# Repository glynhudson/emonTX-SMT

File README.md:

emonTX-SMT
==========

Very early prototype 

openenergymonitor.org

http://openenergymonitor.blogspot.co.uk/search/label/emonTxSMT
http://openenergymonitor.org/emon/node/736

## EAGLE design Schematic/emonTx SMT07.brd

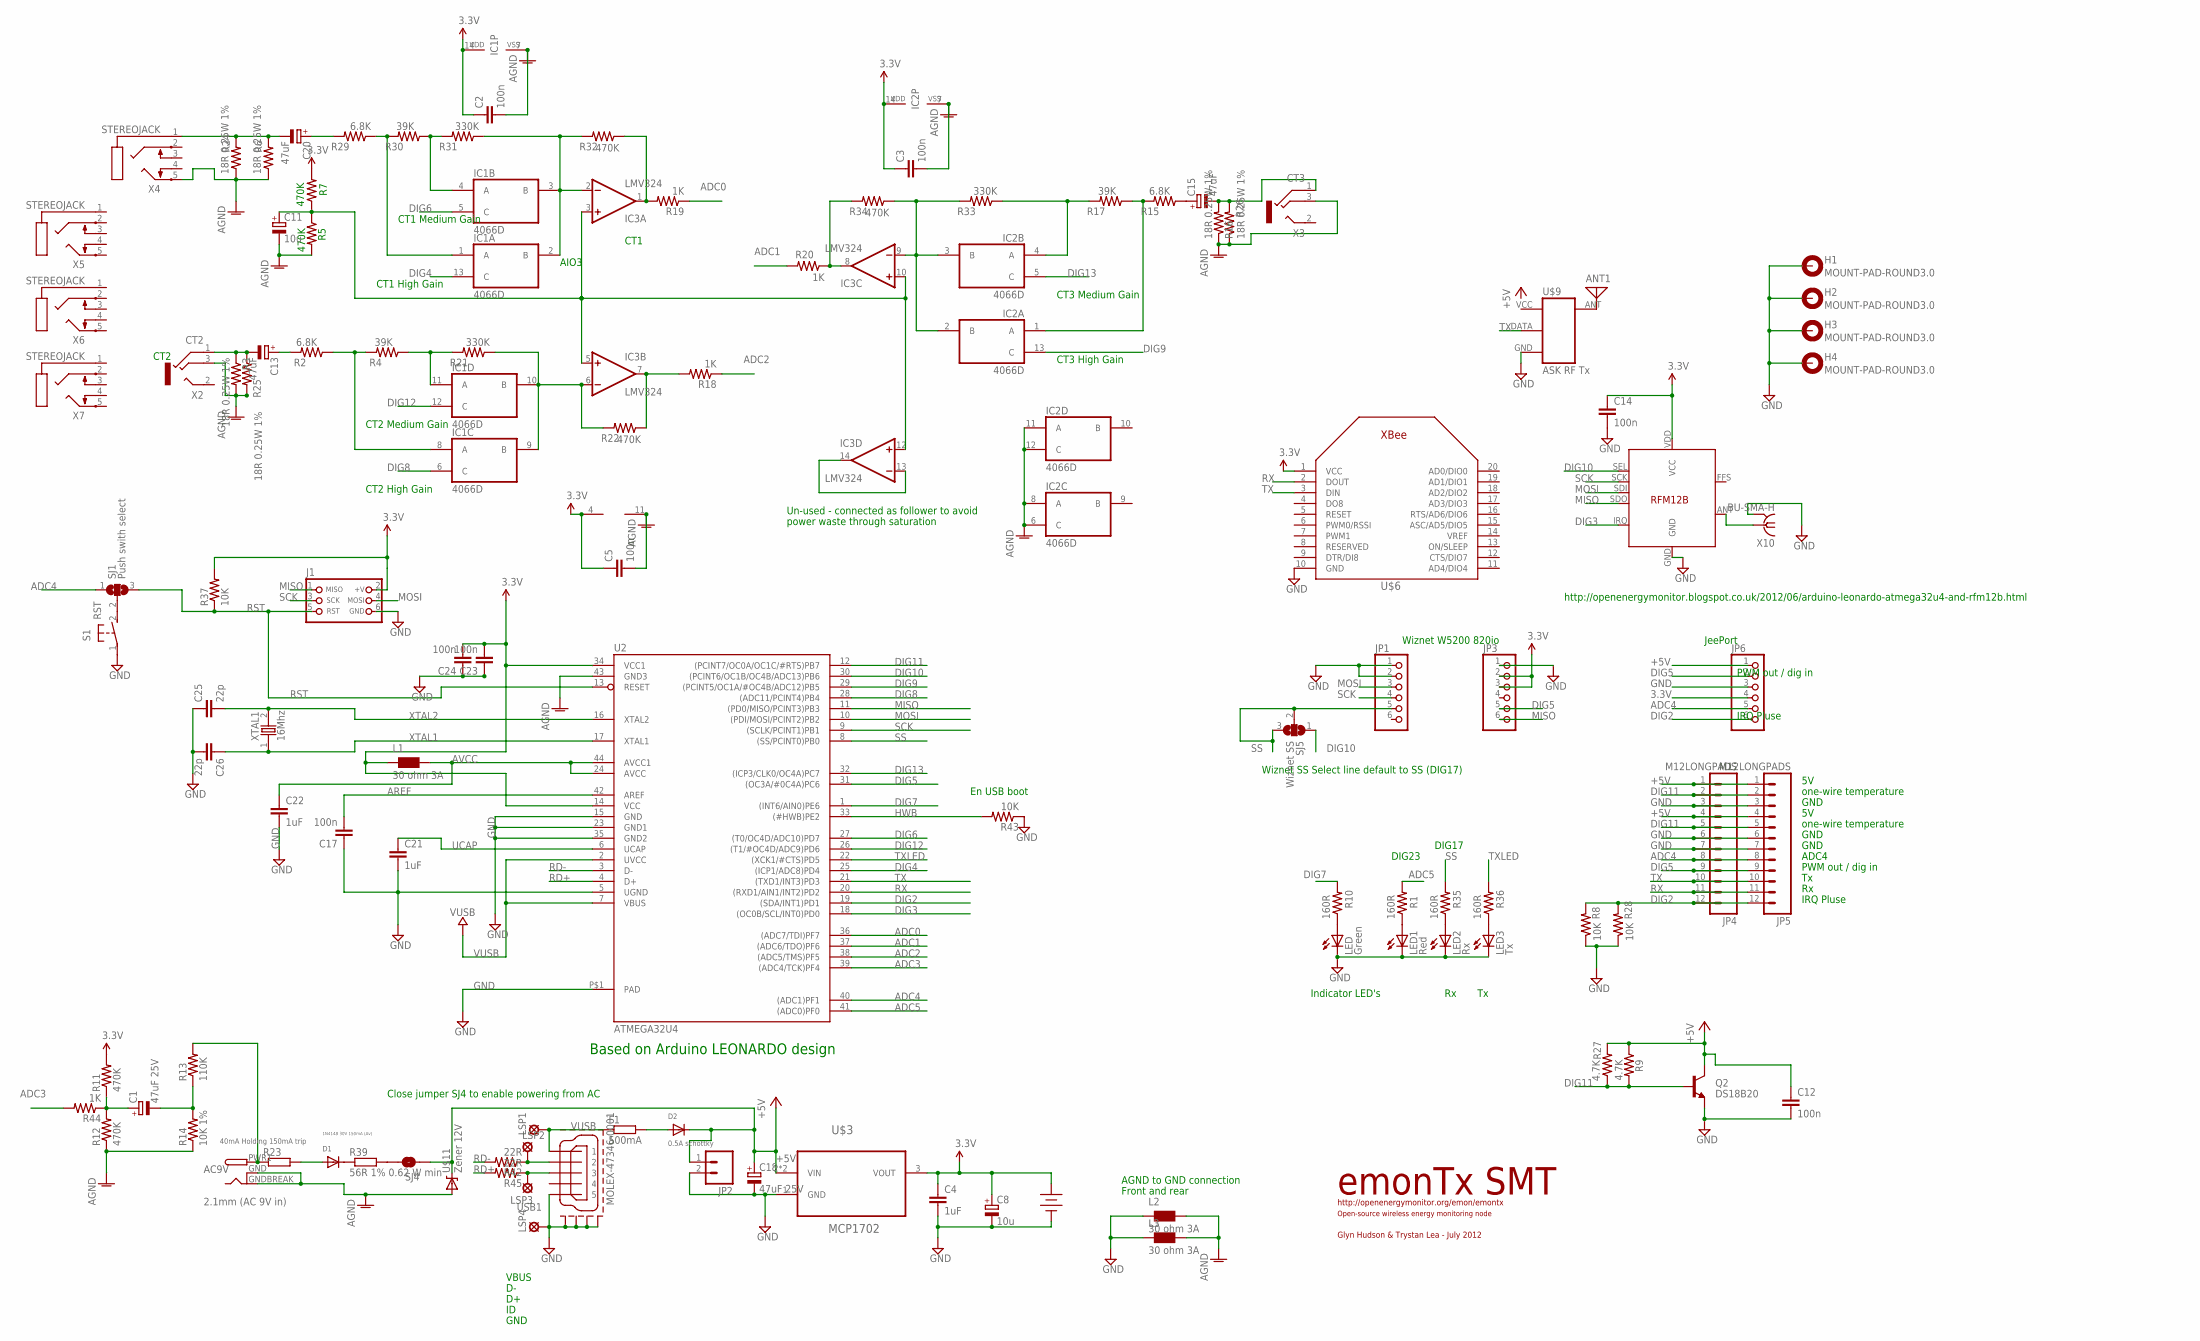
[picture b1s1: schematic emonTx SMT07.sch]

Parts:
3XAAA: 4.5V; AAA_PCB_HOLDER
AC9V: 2.1mm (AC 9V in); DCJACK_2MM_SMT
ANT1: ANTENNA; PAD-01
C1, C18: 47uF 25V; PANASONIC_D
C2, C3, C5, C12, C14, C17, C23, C24: 100n; 0603-CAP
C4: 1uF; C0603
C8, C11: 10u; PANASONIC_B
C13, C15, C20: 47uF; PANASONIC_D
C21: 1uF; 0603-CAP
C22: 1uF; C0603-ROUND
C25, C26: 22p; 0603-CAP
D1: 1N4148 30V 150mA (Av); SOD-323F
D2: 0.5A schottky; SOD-123
F1: 500mA; R1210
H1, H2, H3, H4: MOUNT-PAD-ROUND3.0; 3,0-PAD
IC1, IC2: 4066D; SO14
IC3: LMV324; SO14
J1: CON_HEADER_PRG_AVR_ICSP; HEADER_PRG_2X03
JP1, JP3, JP6: PINHD-1X6; 1X06
JP2: M02LOCK_LONGPADS; 1X02_LOCK_LONGPADS
JP4, JP5: M12LONGPADS; 1X12_LONGPADS
L1, L2, L3: 30 ohm 3A; 0603
LED: Green; CHIPLED_0603
LED1: Red; CHIPLED_0603
LED2: Rx; CHIPLED_0603
LED3: Tx; CHIPLED_0603
LSP1, LSP2, LSP3, LSP4: LSP11
Q2: DS18B20; TO-92
R1, R10, R35, R36: 160R; 0603-RES
R2, R15, R29: 6.8K; 0603-RES
R3, R6, R16: 18R 0.25W 1%; 1206
R4, R17, R30: 39K; 0603-RES
R5, R7, R11, R12, R22, R32, R34: 470K; 0603-RES
R8, R37, R43: 10K; 0603-RES
R9: 4.7K; 1206
R13: 110K; 0603-RES
R14: 10K 1%; 0603-RES
R18, R19, R20, R44: 1K; 0603-RES
R21, R31, R33: 330K; 0603-RES
R23: 40mA Holding 150mA trip; R1210
R24, R25, R26: 18R 0.25W 1%; AXIAL-0.4
R27: 4.7K; AXIAL-0.4
R28: 10K; AXIAL-0.4
R39: 56R 1% 0.62 W min; RESISTOR_R2010
R42, R45: 22R; 0603-RES
S1: RST; B3F-31XX
SJ1: Push swith select; SJ_2W
SJ4: SOLDERJUMPER-OLDNO; SJ_2S-NO
SJ5: Wiznet SS; SJ_2W
U2: ATMEGA32U4; TQFP44-PAD
U$1: RFM12B
U$3: MCP1702; SOT89
U$6: XBEE
U$9: ASK RF Tx; RF-LINK_TX
U$11: Zener 12V; SOD-323
USB1: MOLEX-47346-0001; MOLEX-47364-0001
X2: CT2; 1503_02
X3: CT3; 1503_02
X4, X5, X6, X7: STEREOJACK; STX3100
X10: BU-SMA-H
XTAL1: 16Mhz; HC-49U

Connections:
3.3V: 3XAAA.+, C2.1, C3.1, C4.1, C5.1, C8.+, C14.1, C23.2, C24.2, IC1.14 (VDD), IC2.14 (VDD), IC3.4 (V+), J1.2 (+V), JP3.2, JP3.3, JP6.4, L1.1, R7.2, R11.2, R37.2, U2.14 (VCC), U2.34 (VCC1), U$1.VDD (VCC), U$3.3 (VOUT), U$6.1 (VCC)
+5V: C12.1, C18.+, D2.C, JP2.1, JP4.1, JP4.4, JP5.1, JP5.4, JP6.1, Q2.3 (C), R9.1, R27.P$2 (2), SJ4.1, U$3.2 (VIN), U$3.2.1 (VIN), U$9.VCC (+5V), U$11.1 (C)
ADC0: R19.1, U2.36 ((ADC7/TDI)PF7)
ADC1: R20.2, U2.37 ((ADC6/TDO)PF6)
ADC2: R18.1, U2.38 ((ADC5/TMS)PF5)
ADC3: R44.2, U2.39 ((ADC4/TCK)PF4)
ADC4: JP4.8, JP5.8, JP6.5, SJ1.1, U2.40 ((ADC1)PF1)
ADC5: R1.2, U2.41 ((ADC0)PF0)
AGND: AC9V.GND (GNDBREAK), AC9V.GNDBREAK (GND), C2.2, C3.2, C5.2, C11.-, IC1.7 (VSS), IC2.6 (C), IC2.7 (VSS), IC2.8 (A), IC2.11 (A), IC2.12 (C), IC3.11 (V-), L2.2, L3.2, R3.2, R5.2, R6.1, R12.1, R14.1, R16.1, R24.P$1 (1), R25.P$2 (2), R26.P$1 (1), U2.43 (GND3), U$11.2 (A), X2.3, X3.3, X4.5
AREF: C17.2, U2.42 (AREF)
AVCC: C22.1, L1.2, U2.24 (AVCC), U2.44 (AVCC1)
DIG2: JP4.12, JP5.12, JP6.6, R8.2, R28.P$2 (2), U2.19 ((SDA/INT1)PD1)
DIG3: U2.18 ((OC0B/SCL/INT0)PD0), U$1.IRQ
DIG4: IC1.13 (C), U2.25 ((ICP1/ADC8)PD4)
DIG5: JP3.5, JP4.9, JP5.9, JP6.2, U2.31 ((OC3A/#0C4A)PC6)
DIG6: IC1.5 (C), U2.27 ((T0/OC4D/ADC10)PD7)
DIG7: R10.2, U2.1 ((INT6/AIN0)PE6)
DIG8: IC1.6 (C), U2.28 ((ADC11/PCINT4)PB4)
DIG9: IC2.13 (C), U2.29 ((PCINT5/OC1A/#OC4B/ADC12)PB5)
DIG10: SJ5.1, U2.30 ((PCINT6/OC1B/OC4B/ADC13)PB6), U$1.SEL
DIG11: JP4.2, JP4.5, JP5.2, JP5.5, Q2.2 (B), R9.2, R27.P$1 (1), U2.12 ((PCINT7/OC0A/OC1C/#RTS)PB7)
DIG12: IC1.12 (C), U2.26 ((T1/#OC4D/ADC9)PD6)
DIG13: IC2.5 (C), U2.32 ((ICP3/CLK0/OC4A)PC7)
GND: 3XAAA.-, C4.2, C8.-, C12.2, C14.2, C17.1, C18.-, C21.2, C22.2, C23.1, C24.1, C25.1, C26.2, H1.B3,0, H2.B3,0, H3.B3,0, H4.B3,0, J1.6 (GND), JP1.1, JP1.2, JP2.2, JP3.1, JP4.3, JP4.6, JP4.7, JP5.3, JP5.6, JP5.7, JP6.3, L2.1, L3.1, LED.C, LED1.C, LED2.C, LED3.C, LSP4.MP, Q2.1 (E), R8.1, R28.P$1 (1), R43.1, S1.1, U2.5 (UGND), U2.15 (GND), U2.23 (GND1), U2.35 (GND2), U2.P$1 (PAD), U$1.GND, U$3.1 (GND), U$6.10 (GND), U$9.GND, USB1.5, USB1.GND1, USB1.GND2, USB1.GND3, USB1.GND4, X10.2 (GND), X10.3 (GND), X10.4 (GND), X10.5 (GND)
HWB: R43.2, U2.33 ((#HWB)PE2)
MISO: J1.1 (MISO), JP3.6, U2.11 ((PD0/MISO/PCINT3)PB3), U$1.SDO
MOSI: J1.4 (MOSI), JP1.3, U2.10 ((PDI/MOSI/PCINT2)PB2), U$1.SDI
unnamed: S1.2 (S), SJ1.2
unnamed: LED.A, R10.1
unnamed: AC9V.PWR1 (PWR), R13.2, R23.1
unnamed: D2.A, F1.2
unnamed: C1.-, R13.1, R14.2
unnamed: D1.C, R39.1
unnamed: C20.+, R29.2
unnamed: LED1.A, R1.1
unnamed: C1.+, R11.1, R12.2, R44.1
unnamed: R39.2, SJ4.2
unnamed: ANT1.1, U$9.ANT
unnamed: LSP2.MP, R42.1, USB1.2
unnamed: U$1.ANT, X10.1
unnamed: C15.-, R16.2, R26.P$2 (2), X3.1
unnamed: LSP3.MP, R45.1, USB1.3
unnamed: IC1.4 (A), R30.1, R31.2
unnamed: IC1.1 (A), R29.1, R30.2
unnamed: C13.+, R2.2
unnamed: LED2.A, R35.1
unnamed: C13.-, R3.1, R25.P$1 (1), X2.1
unnamed: C20.-, R6.2, R24.P$2 (2), X4.1
unnamed: C11.+, IC3.3 (+IN), IC3.5 (+IN), IC3.10 (+IN), IC3.12 (+IN), R5.1, R7.1
unnamed: C15.+, R15.1
unnamed: IC1.8 (A), R2.1, R4.2
unnamed: IC1.11 (A), R4.1, R21.2
unnamed: IC3.7 (OUT), R18.2, R22.1
unnamed: IC1.9 (B), IC1.10 (B), IC3.6 (-IN), R21.1, R22.2
unnamed: IC1.2 (B), IC1.3 (B), IC3.2 (-IN), R31.1, R32.2
unnamed: IC3.1 (OUT), R19.2, R32.1
unnamed: LED3.A, R36.1
unnamed: IC2.2 (B), IC2.3 (B), IC3.9 (-IN), R33.2, R34.1
unnamed: IC3.13 (-IN), IC3.14 (OUT)
unnamed: IC3.8 (OUT), R20.1, R34.2
unnamed: IC2.1 (A), R15.2, R17.1
unnamed: IC2.4 (A), R17.2, R33.1
unnamed: D1.A, R23.2
RD+: R45.2, U2.4 (D+)
RD-: R42.2, U2.3 (D-)
RST: J1.5 (RST), R37.1, SJ1.3, U2.13 (RESET)
RX: JP4.11, JP5.11, U2.20 ((RXD1/AIN1/INT2)PD2), U$6.2 (DOUT)
SCK: J1.3 (SCK), JP1.4, U2.9 ((SCLK/PCINT1)PB1), U$1.SCK
SS: JP1.5, R35.2, SJ5.2, SJ5.3, U2.8 ((SS/PCINT0)PB0)
TX: JP4.10, JP5.10, U2.21 ((TXD1/INT3)PD3), U$6.3 (DIN), U$9.DATA
TXLED: R36.2, U2.22 ((XCK1/#CTS)PD5)
UCAP: C21.1, U2.6 (UCAP)
VUSB: F1.1, LSP1.MP, U2.2 (UVCC), U2.7 (VBUS), USB1.1
XTAL1: C26.1, U2.17 (XTAL1), XTAL1.1
XTAL2: C25.2, U2.16 (XTAL2), XTAL1.2

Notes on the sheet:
CT2
CT1
http://openenergymonitor.org/emon/emontx
Open-source wireless energy monitoring node
emonTx SMT
Glyn Hudson & Trystan Lea - July 2012
AIO3
Based on Arduino LEONARDO design
Wiznet W5200 820io
Close jumper SJ4 to enable powering from AC
En USB boot
Wiznet SS Select line default to SS (DIG17)
CT1 High Gain
CT1 Medium Gain
DIG23
http://openenergymonitor.blogspot.co.uk/2012/06/arduino-leonardo-atmega32u4-and-rfm12b.html
CT2 Medium Gain
CT2 High Gain
CT3 Medium Gain
CT3 High Gain
PWM out / dig in
IRQ Pluse
AGND to GND connection
Front and rear
ADC4
one-wire temperature
GND
VBUS
Indicator LED's
Rx Tx
Un-used - connected as follower to avoid
power waste through saturation
DIG17
JeePort

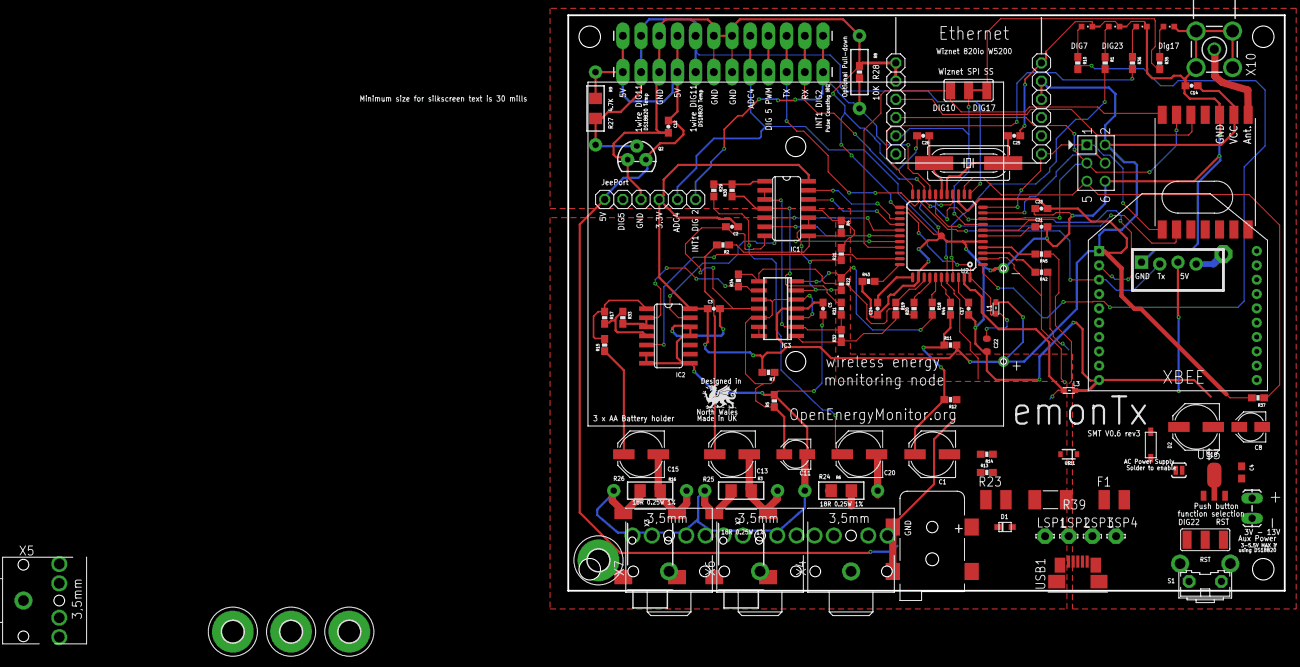
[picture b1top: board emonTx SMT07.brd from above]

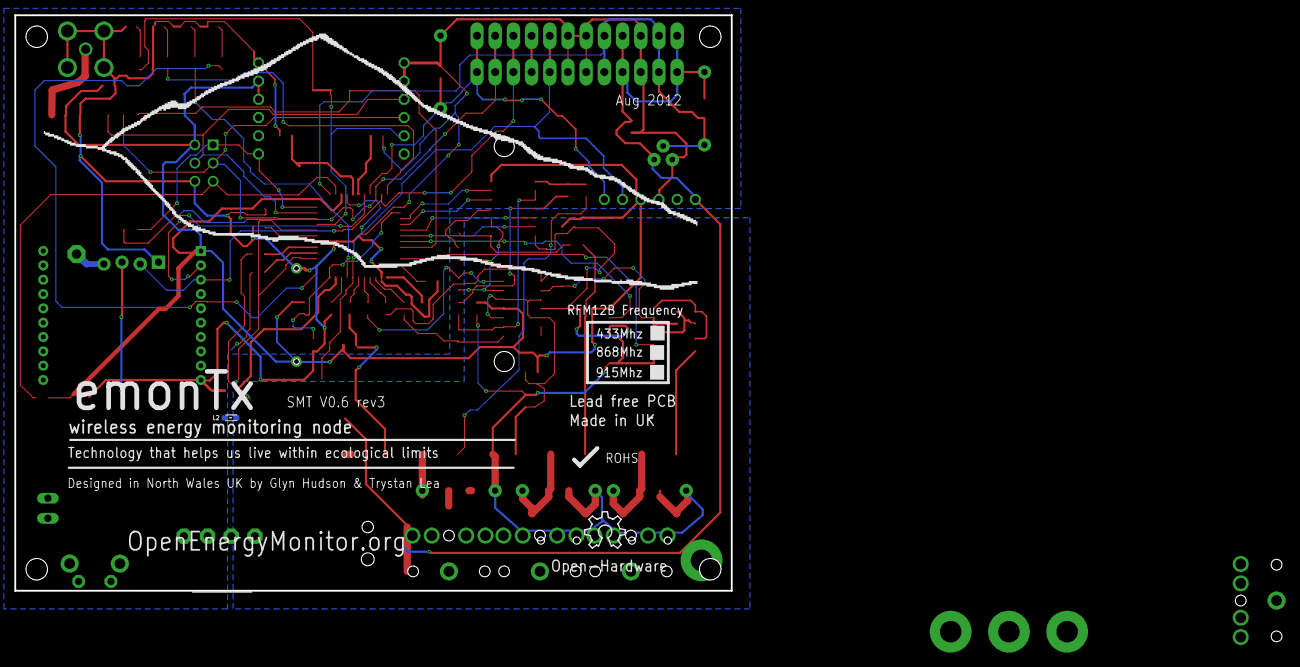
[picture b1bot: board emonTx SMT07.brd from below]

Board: 2 copper layers, 100.0 x 80.3 mm, 115 parts (3 on the bottom side), 75 nets.

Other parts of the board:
U$2: Open-source Hardware; OSHW_8X200_NOTEXT
U$5: CNICHT

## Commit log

2012-09-17 first commit at V0.6.5
2012-09-17 route uvcc to connect to USB 5V
2012-09-21 update schotkey reverse blocking diode pcb footprint to SOD-123
2012-10-02 added testing firmware examples
2012-10-05 add tru-hole 3.5mm to BOM
2012-10-09 connect wiznet reset to dig5, need to route
